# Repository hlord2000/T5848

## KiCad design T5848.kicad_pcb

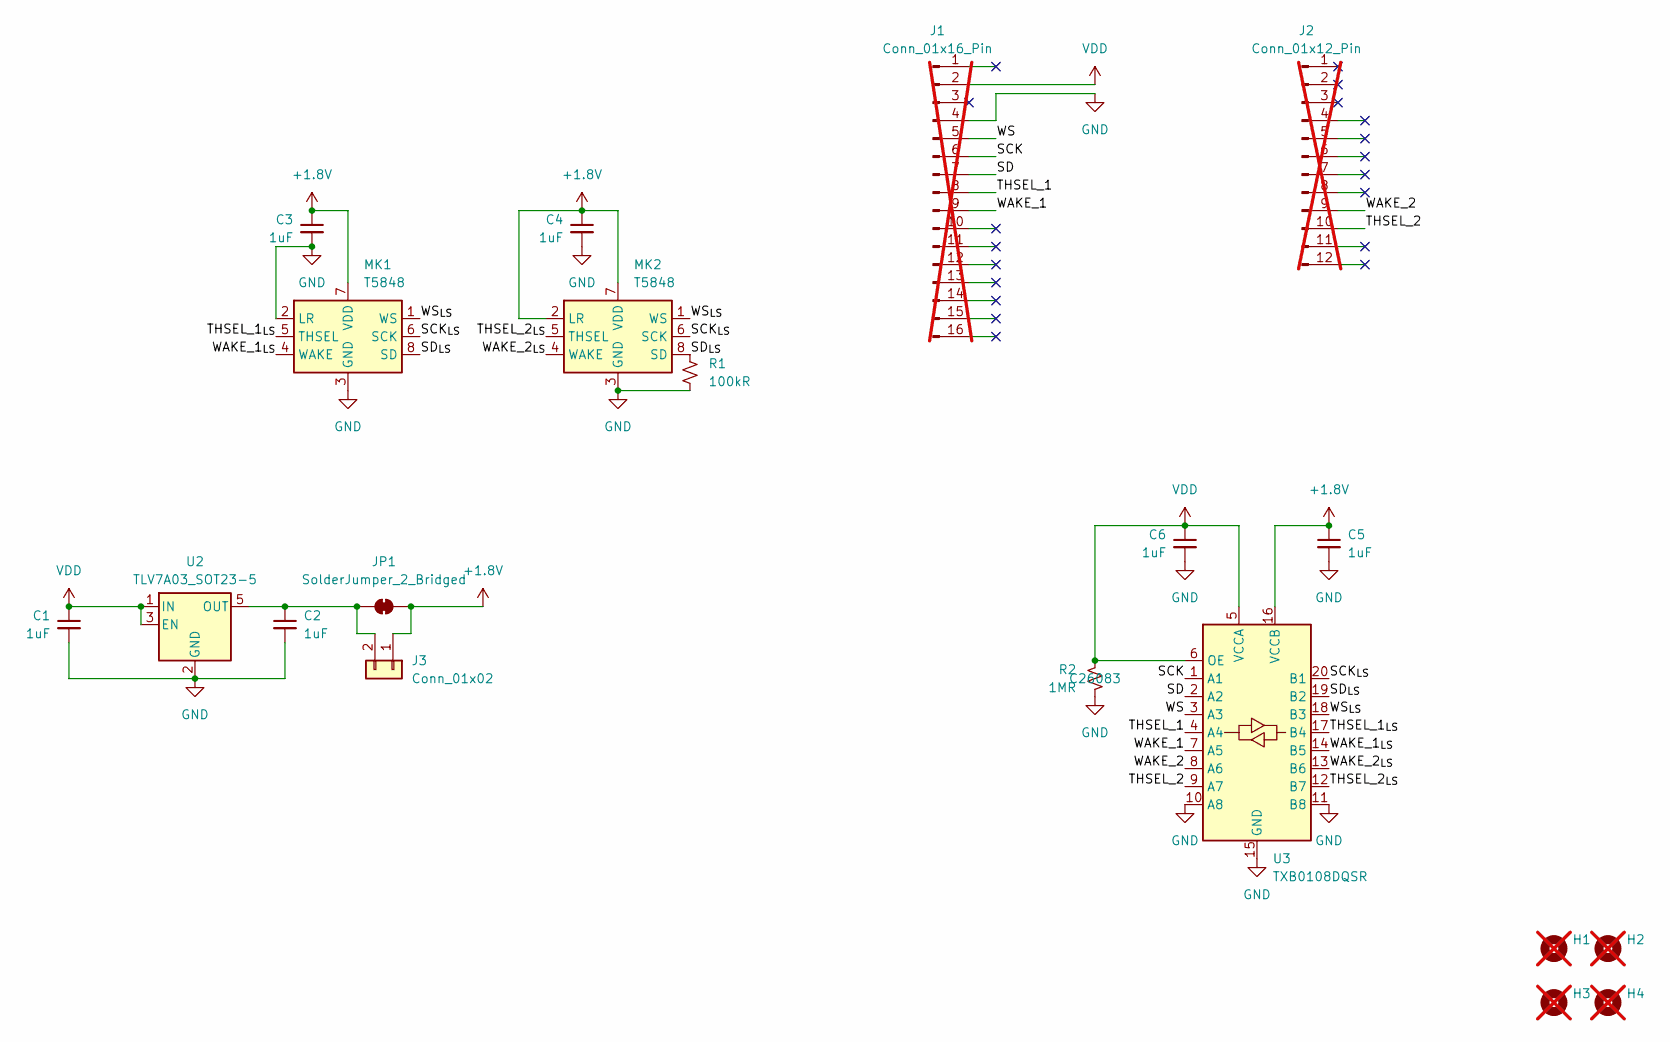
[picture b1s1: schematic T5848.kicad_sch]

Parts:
C1, C2, C3, C4, C5, C6: 1uF; C_0402_1005Metric; LCSC C52923
H1, H2, H3, H4: MountingHole; MountingHole_2.5mm; not fitted
J1: Conn_01x16_Pin; PinHeader_1x16_P2.54mm_Vertical; not fitted
J2: Conn_01x12_Pin; PinHeader_1x12_P2.54mm_Vertical; not fitted
J3: Conn_01x02; PinHeader_1x02_P2.54mm_Vertical
JP1: SolderJumper_2_Bridged; SolderJumper-2_P1.3mm_Bridged_RoundedPad1.0x1.5mm
MK1, MK2: T5848; TDK_T5848-8_3.5x2.65mm; LCSC C20344623
R1: 100kR; R_0402_1005Metric; LCSC C25741
R2: 1MR; R_0402_1005Metric; LCSC C26083
U2: TLV7A03_SOT23-5; SOT-23-5; LCSC C92498
U3: TXB0108DQSR; USON-20_2x4mm_P0.4mm; LCSC C427057

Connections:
+1.8V: C3.1, C4.1, C5.1, J3.1, JP1.2 (B), MK1.7 (VDD), MK2.2 (LR), MK2.7 (VDD), U3.16 (VCCB)
/SCK: J1.6, U3.1 (A1)
/SCK_{LS}: MK1.6 (SCK), MK2.6 (SCK), U3.20 (B1)
/SD: J1.7, U3.2 (A2)
/SD_{LS}: MK1.8 (SD), MK2.8 (SD), R1.1, U3.19 (B2)
/THSEL_1: J1.8, U3.4 (A4)
/THSEL_1_{LS}: MK1.5 (THSEL), U3.17 (B4)
/THSEL_2: J2.10, U3.9 (A7)
/THSEL_2_{LS}: MK2.5 (THSEL), U3.12 (B7)
/WAKE_1: J1.9, U3.7 (A5)
/WAKE_1_{LS}: MK1.4 (WAKE), U3.14 (B5)
/WAKE_2: J2.9, U3.8 (A6)
/WAKE_2_{LS}: MK2.4 (WAKE), U3.13 (B6)
/WS: J1.5, U3.3 (A3)
/WS_{LS}: MK1.1 (WS), MK2.1 (WS), U3.18 (B3)
GND: C1.2, C2.2, C3.2, C4.2, C5.2, C6.2, J1.4, MK1.2 (LR), MK1.3 (GND), MK2.3 (GND), R1.2, R2.2, U2.2 (GND), U3.10 (A8), U3.11 (B8), U3.15 (GND)
unnamed: C2.1, J3.2, JP1.1 (A), U2.5 (OUT)
VDD: C1.1, C6.1, J1.2, R2.1, U2.1 (IN), U2.3 (EN), U3.5 (VCCA), U3.6 (OE)

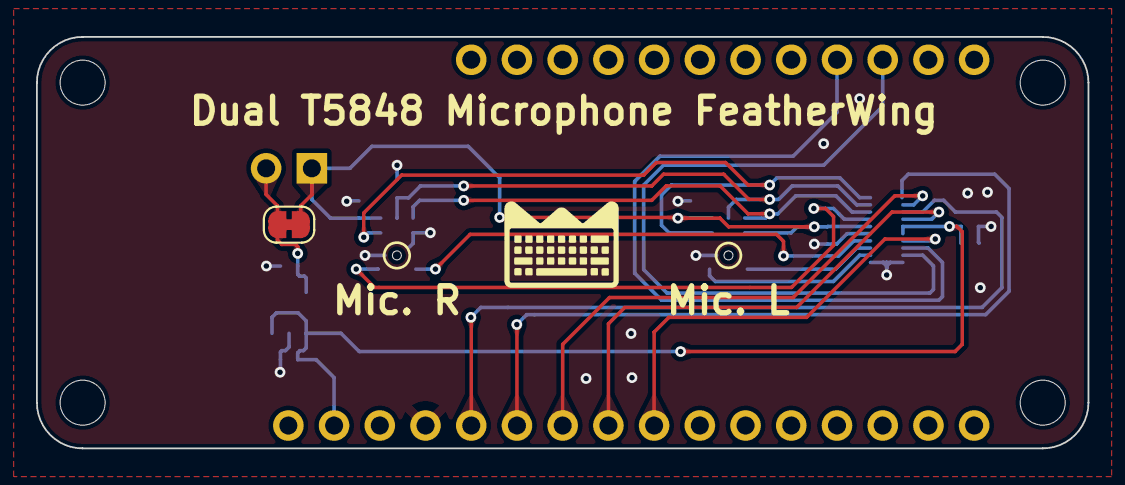
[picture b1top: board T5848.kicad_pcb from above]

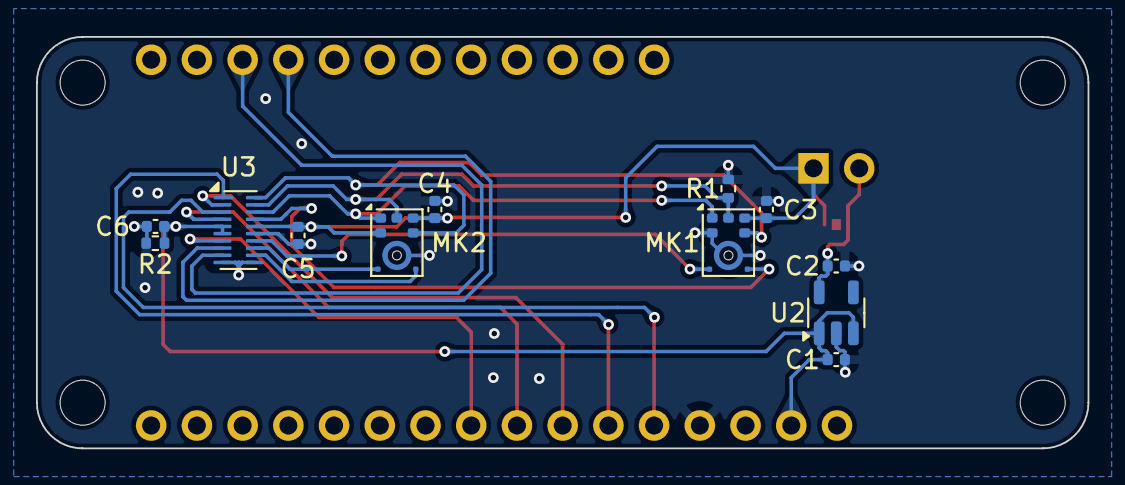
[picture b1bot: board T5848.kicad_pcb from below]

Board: 4 copper layers, 58.4 x 22.9 mm, 20 parts (14 on the bottom side), 18 nets.

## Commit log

2025-07-28 Initial commit.
